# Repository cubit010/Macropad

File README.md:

# Macropad
macropad
# Cad

# PCB

# Schematic

# Case by itself

Friction fitted (with clearance designed for 3d printing (I can print this myself, but some filament could be nice)

# Firmware
- KMK based and currently don't have specified macros yet, screen is yet to be determined for use but probably used for volume bar animations at least 
# BOM
- 1x SEEEDUINO XIAO RP2040
- 9x MX style switches (5 pin preferred)
- 9x Through-hole 1N4148 diodes
- 1x SSD1306 128x32 OLED 0.91"
- 4x SK6812-MINI-E LED
- 9x Blank DSA Keycaps
- 1x 1x4 2.54mm female header (for boosting height for the display

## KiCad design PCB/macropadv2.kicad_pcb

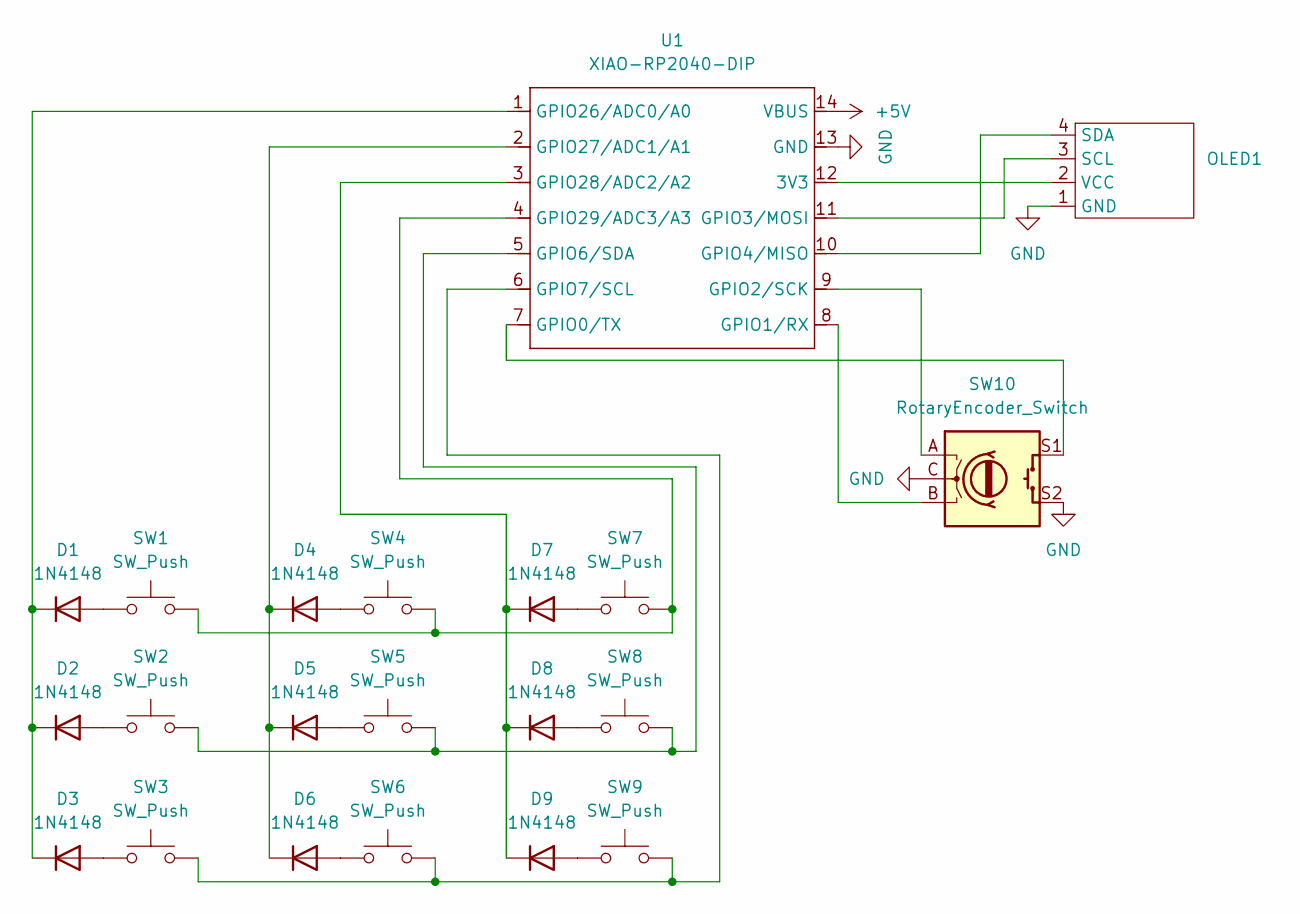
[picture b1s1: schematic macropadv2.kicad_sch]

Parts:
D1, D2, D3, D4, D5, D6, D7, D8, D9: 1N4148; D_DO-35_SOD27_P7.62mm_Horizontal
OLED1: SSD1306-0.91-OLED-4pin-128x32
SW1, SW2, SW3, SW4, SW5, SW6, SW7, SW8, SW9: SW_Push; SW_Cherry_MX_1.00u_PCB
SW10: RotaryEncoder_Switch; RotaryEncoder_Alps_EC11E-Switch_Vertical_H20mm
U1: XIAO-RP2040-DIP

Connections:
+5V: U1.14 (VBUS)
GND: OLED1.1 (GND), SW10.C, SW10.S2, U1.13 (GND)
unnamed: D1.2 (A), SW1.1
unnamed: D1.1 (K), D2.1 (K), D3.1 (K), U1.1 (GPIO26/ADC0/A0)
unnamed: D2.2 (A), SW2.1
unnamed: D3.2 (A), SW3.1
unnamed: D4.2 (A), SW4.1
unnamed: D4.1 (K), D5.1 (K), D6.1 (K), U1.2 (GPIO27/ADC1/A1)
unnamed: D5.2 (A), SW5.1
unnamed: D6.2 (A), SW6.1
unnamed: D7.2 (A), SW7.1
unnamed: D7.1 (K), D8.1 (K), D9.1 (K), U1.3 (GPIO28/ADC2/A2)
unnamed: D8.2 (A), SW8.1
unnamed: D9.2 (A), SW9.1
unnamed: OLED1.4 (SDA), U1.10 (GPIO4/MISO)
unnamed: OLED1.2 (VCC), U1.12 (3V3)
unnamed: OLED1.3 (SCL), U1.11 (GPIO3/MOSI)
unnamed: SW10.S1, U1.7 (GPIO0/TX)
unnamed: SW10.B, U1.8 (GPIO1/RX)
unnamed: SW10.A, U1.9 (GPIO2/SCK)
unnamed: SW2.2, SW5.2, SW8.2, U1.5 (GPIO6/SDA)
unnamed: SW3.2, SW6.2, SW9.2, U1.6 (GPIO7/SCL)
unnamed: SW1.2, SW4.2, SW7.2, U1.4 (GPIO29/ADC3/A3)

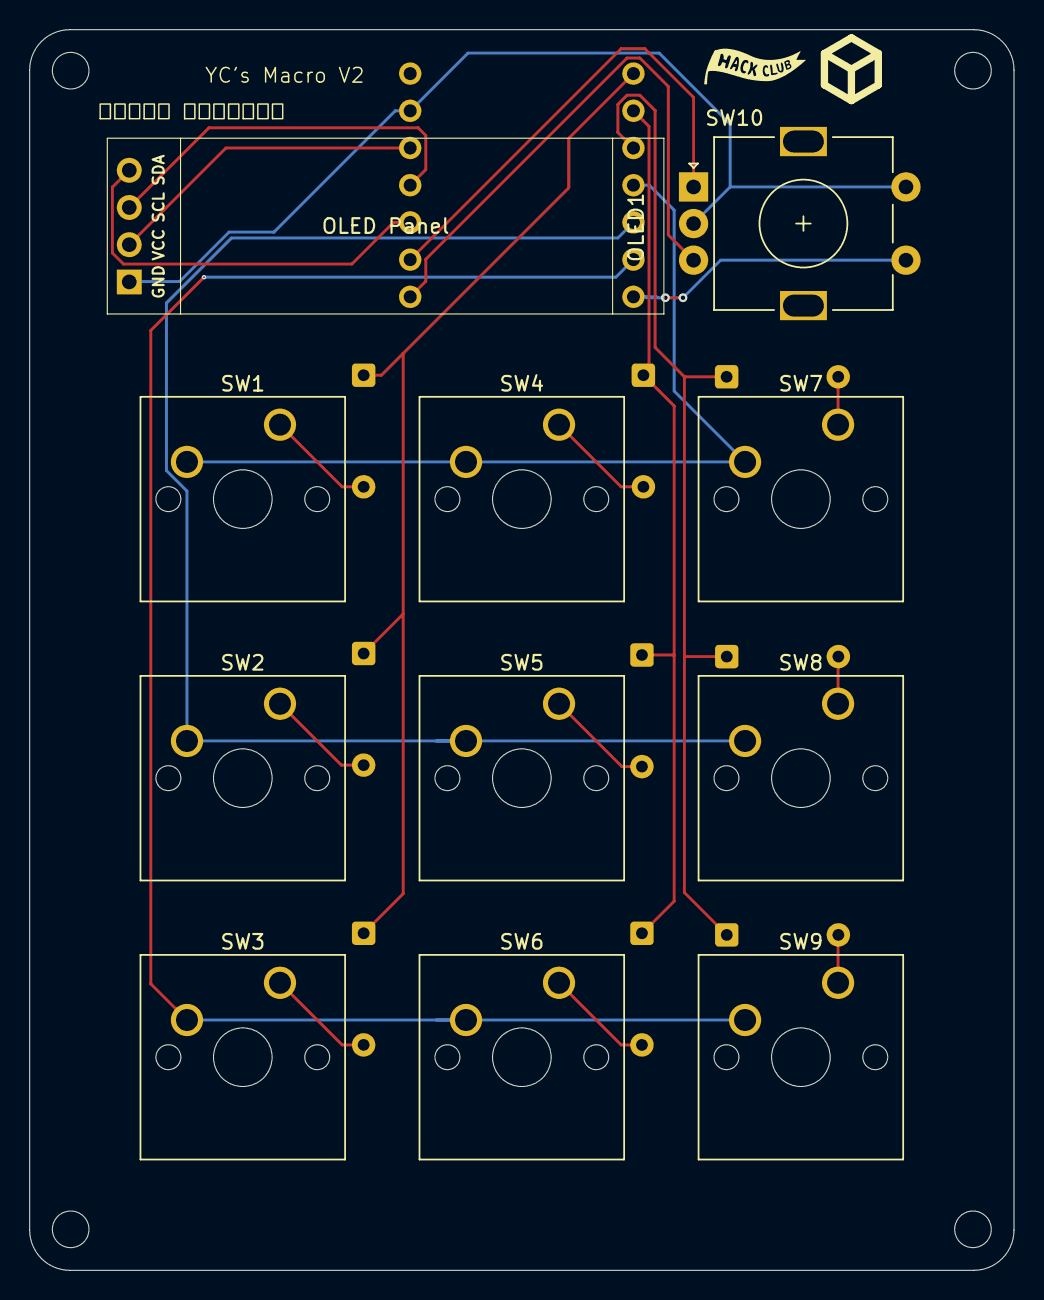
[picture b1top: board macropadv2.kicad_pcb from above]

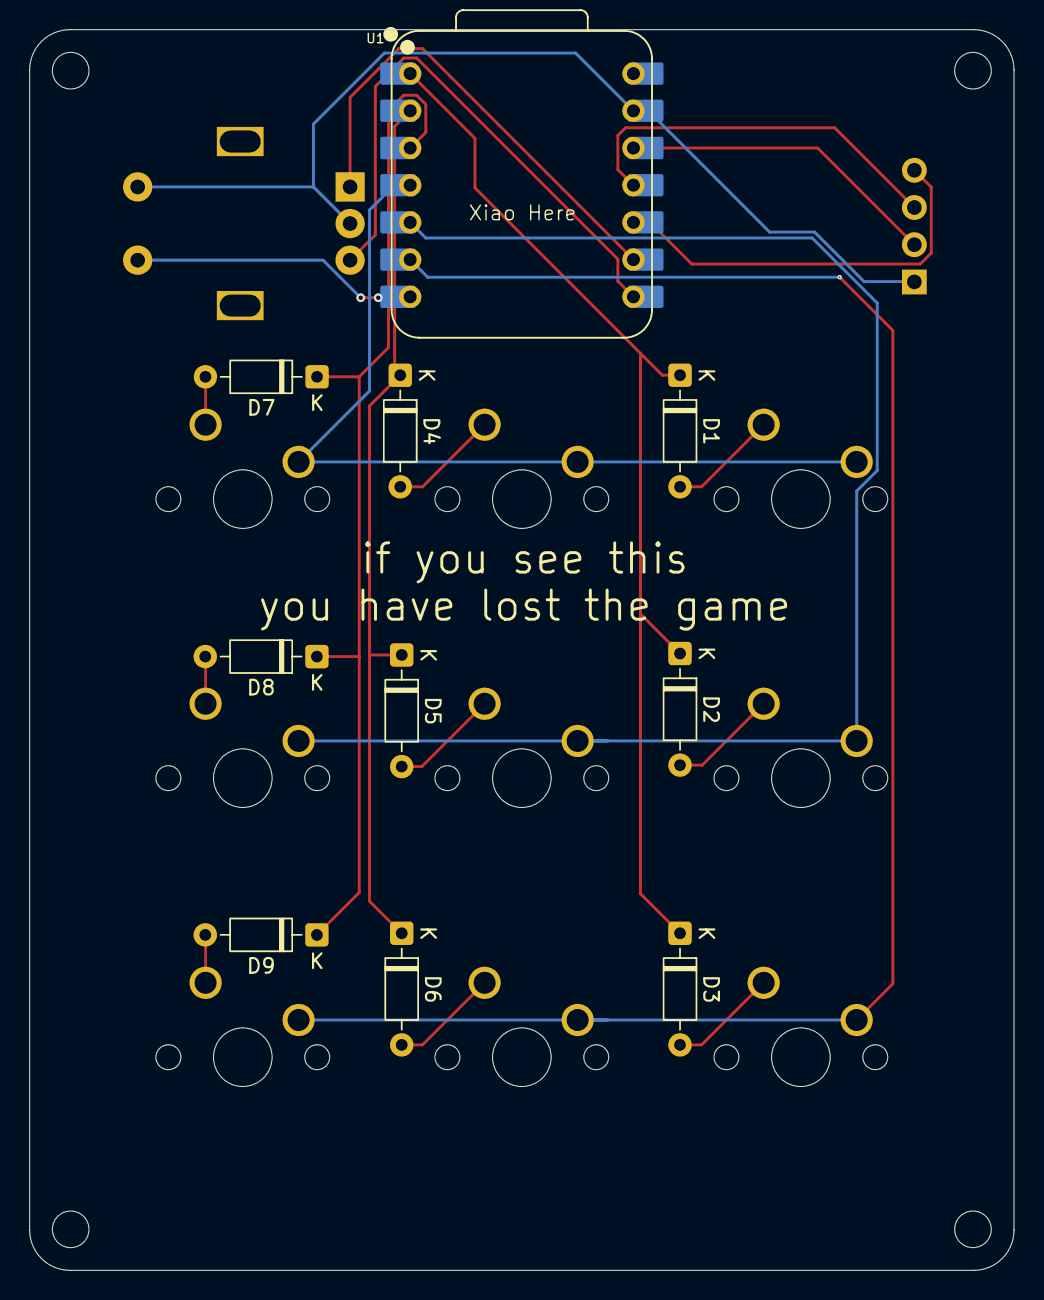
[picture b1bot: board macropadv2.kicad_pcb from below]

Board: 2 copper layers, 67.2 x 84.7 mm, 21 parts (10 on the bottom side), 22 nets.

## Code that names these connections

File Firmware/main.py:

# KMK firmware example for Seeed RP2040 macropad
# Columns: GPIO29, GPIO6, GPIO7 (pins 4,5,6)
# Rows: GPIO26, GPIO27, GPIO28 (pins 1,2,3)
import board

from kmk.kmk_keyboard import KMKKeyboard
from kmk.keys import KC
from kmk.scanners import DiodeOrientation


keyboard = KMKKeyboard()

# Pin definitions
keyboard.row_pins = (board.GP29, board.GP6, board.GP7)
keyboard.col_pins = (board.GP26, board.GP27, board.GP28)
keyboard.diode_orientation = DiodeOrientation.ROW2COL


# Rotary Encoder
from kmk.modules.encoder import EncoderHandler
encoder_handler = EncoderHandler()
keyboard.modules.append(encoder_handler)
encoder_handler.pins = ((2, 1),)
encoder_handler.switch_pin = 0
encoder_handler.map = [((KC.VOLU,), (KC.VOLD,))]

# OLED Display
from kmk.extensions.display import Oled
keyboard.extensions.append(
    Oled(
        width=128,
        height=32,
        i2c_num=0,
        sda=board.GP4,
        scl=board.GP3,
    )
)

# Custom Volume Bar UI
from kmk.extensions.display import Oled, Canvas

class VolumeUI(Canvas):
    def __init__(self):
        super().__init__(128, 32)
        self.level = 50

    def draw(self, display):
        display.fill(0)
        bar_width = int((self.level / 100) * 120)
        display.rect(4, 12, 120, 8, 1)
        display.fill_rect(4, 12, bar_width, 8, 1)
        display.text(f"Vol {self.level}", 4, 0, 1)
        display.show()

vol_ui = VolumeUI()

oled = Oled(
    width=128,
    height=32,
    i2c_num=0,
    sda=4,
    scl=3,
    display=vol_ui,
)
keyboard.extensions.append(oled)

# Update encoder mapping to change volume level
encoder_handler.map = [
    ((lambda: setattr(vol_ui, "level", min(100, vol_ui.level + 1)),),
     (lambda: setattr(vol_ui, "level", max(0, vol_ui.level - 1)),))
]

# Simple 3x3 keymap
keyboard.keymap = [
    [KC.A, KC.B, KC.C],
    [KC.D, KC.E, KC.F],
    [KC.G, KC.H, KC.I],
]

if __name__ == '__main__':
    keyboard.go()

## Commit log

2025-11-30 Fix formatting of BOM section in README
2025-11-30 Revise README formatting and content clarity
    Updated section headers and improved text clarity in the README.
2025-11-30 add component
2025-12-01 add source files
